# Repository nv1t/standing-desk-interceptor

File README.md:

# standing-desk-interceptor
I wanted to intercept the communication between my Flexispot E5B standing desk buttons. This is the progress on the project.
It should work on any other flexispot desk as well, as i suspect they use the same button interface with nearly the same protocol. But this needs testing!

# RJ45 Pins
```
1 - RES
2 - SWIM
3 - ?
4 - WAKE
5 - RX
6 - TX
7 - GND
8 - VCC
```

# Using SWIM
The SWIM Debug interface is on the RJ45 Port, but not possible to use, due to set Read Protection, which can only be disabled by overwriting the Chip itself.

# Protocol
Every Command starts with 0x9b and ends with 0x9d. The second byte is the length of the Message with the Endbyte included.

Those are the know commands from the button controller to the motor controller with their respective button names.
```
commands = {
    'reset': '\x9b\x06\x02\x00\x00\x6c\xa1\x9d',
    'Mod2':  '\x9b\x06\x02\x08\x00\xac\xa6\x9d',
    'Mod1':  '\x9b\x06\x02\x04\x00\xac\xa3\x9d',
    'down':  '\x9b\x06\x02\x02\x00\x0c\xa0\x9d',
    'up':    '\x9b\x06\x02\x01\x00\xfc\xa0\x9d'
}
```

Further inspection can be made by intercepting the commands and bit flip to find out where the table height is included.

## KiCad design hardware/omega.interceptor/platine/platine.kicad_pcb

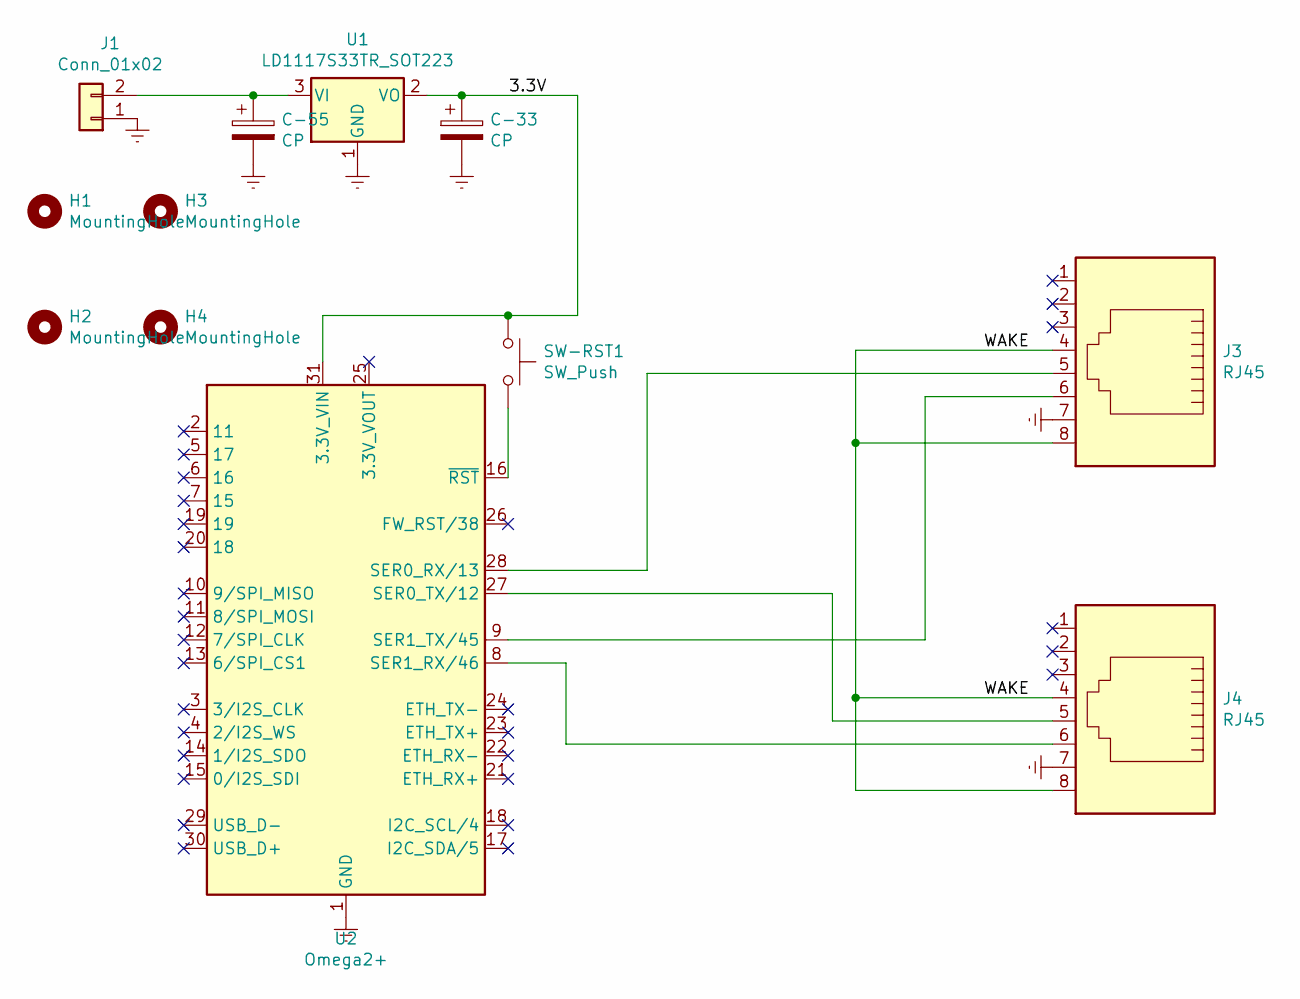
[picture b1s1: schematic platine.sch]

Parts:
C-33, C-55: CP; CP_Radial_D4.0mm_P2.00mm
H1, H2, H3, H4: MountingHole; MountingHole_2.7mm_M2.5
J1: Conn_01x02; PinHeader_1x02_P2.54mm_Vertical
J3, J4: RJ45; MEBP_8-8G
SW-RST1: SW_Push; SW_DIP_SPSTx01_Slide_6.7x4.1mm_W7.62mm_P2.54mm_LowProfile
U1: LD1117S33TR_SOT223; TO-126-3_Horizontal_TabDown
U2: Omega2+; ONION_OMEGA2

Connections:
/3.3V: C-33.1, SW-RST1.1, U1.2 (VO), U2.31 (3.3V_VIN)
/WAKE: J3.4, J3.8, J4.4, J4.8
Earth: C-33.2, C-55.2, J1.1, J3.7, J4.7, U1.1 (GND), U2.1 (GND), U2.32 (GND)
unnamed: C-55.1, J1.2, U1.3 (VI)
unnamed: J3.5, U2.28 (SER0_RX/13)
unnamed: J3.6, U2.9 (SER1_TX/45)
unnamed: J4.5, U2.27 (SER0_TX/12)
unnamed: J4.6, U2.8 (SER1_RX/46)
unnamed: SW-RST1.2, U2.16 (~RST)

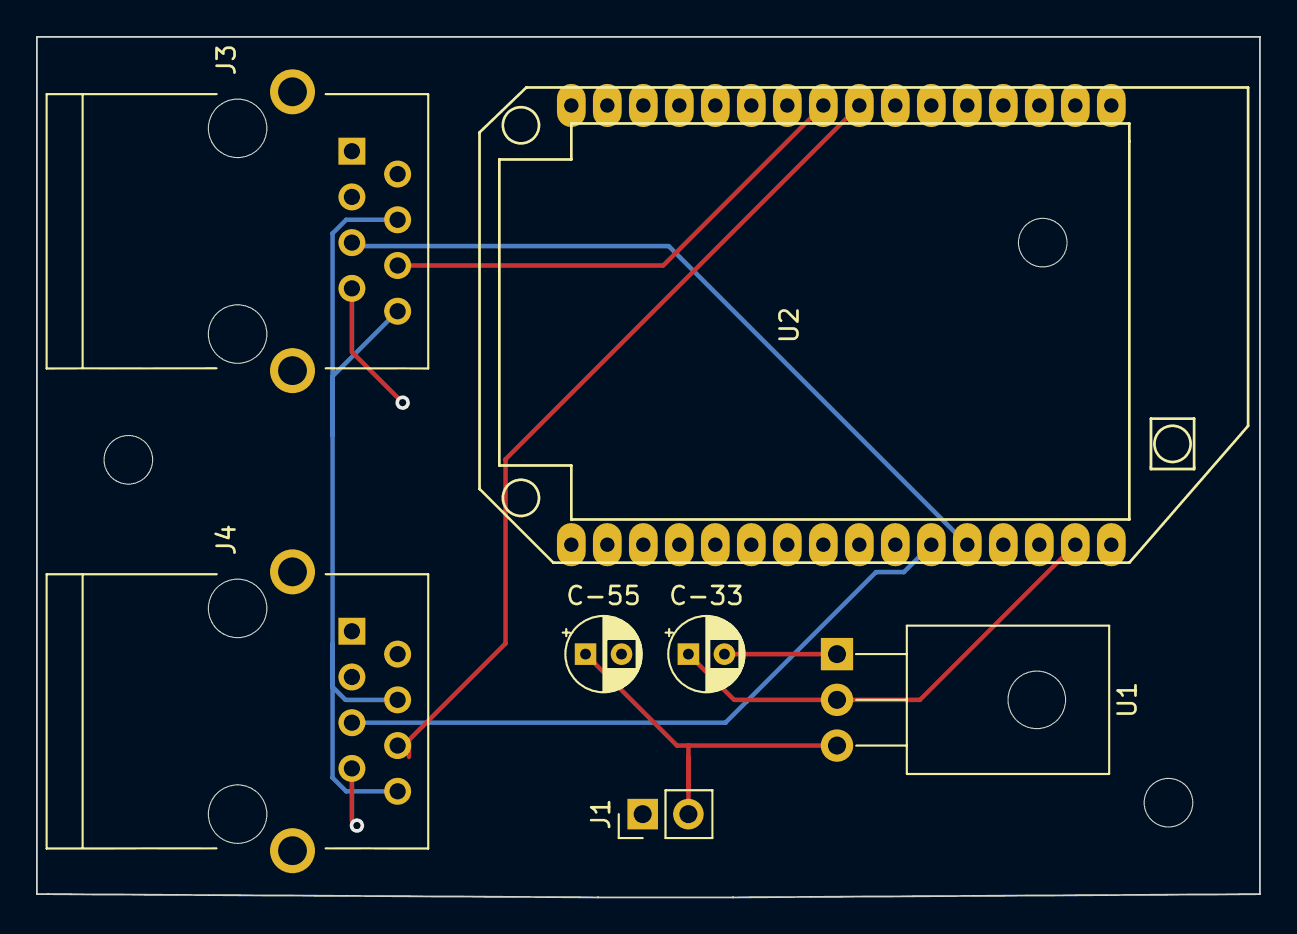
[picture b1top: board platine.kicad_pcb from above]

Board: 2 copper layers, 67.9 x 47.8 mm, 11 parts (0 on the bottom side), 8 nets.

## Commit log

2020-03-28 initial commit with basic files. More will follow in the next few days
2020-03-28 added basic protocol and pin configuration readme
2020-04-02 added a simple omega interceptor schemata.
2020-06-19 Signifikant changes to interceptor hardware layout * removed usb connector * removed switches for interceptor
    made an easy setup to get it manifactured fast and to start testing the protocol
2020-07-08 switched usb devices
2020-07-08 added script to send specific messages to display
2020-07-08 convert messages to binary format
2020-07-08 added recordings for different heights
2020-07-08 changed a few things in intercept
2020-07-08 started decoding protocol message
